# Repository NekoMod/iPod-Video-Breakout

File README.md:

# iPod-Video-Breakout

Breakout board for iPod Video connectors.

It uses our own connectors EAGLE library https://github.com/NekoMod/iPod-Video-Motherboard-Connectors

Pins are raster 2.54mm.

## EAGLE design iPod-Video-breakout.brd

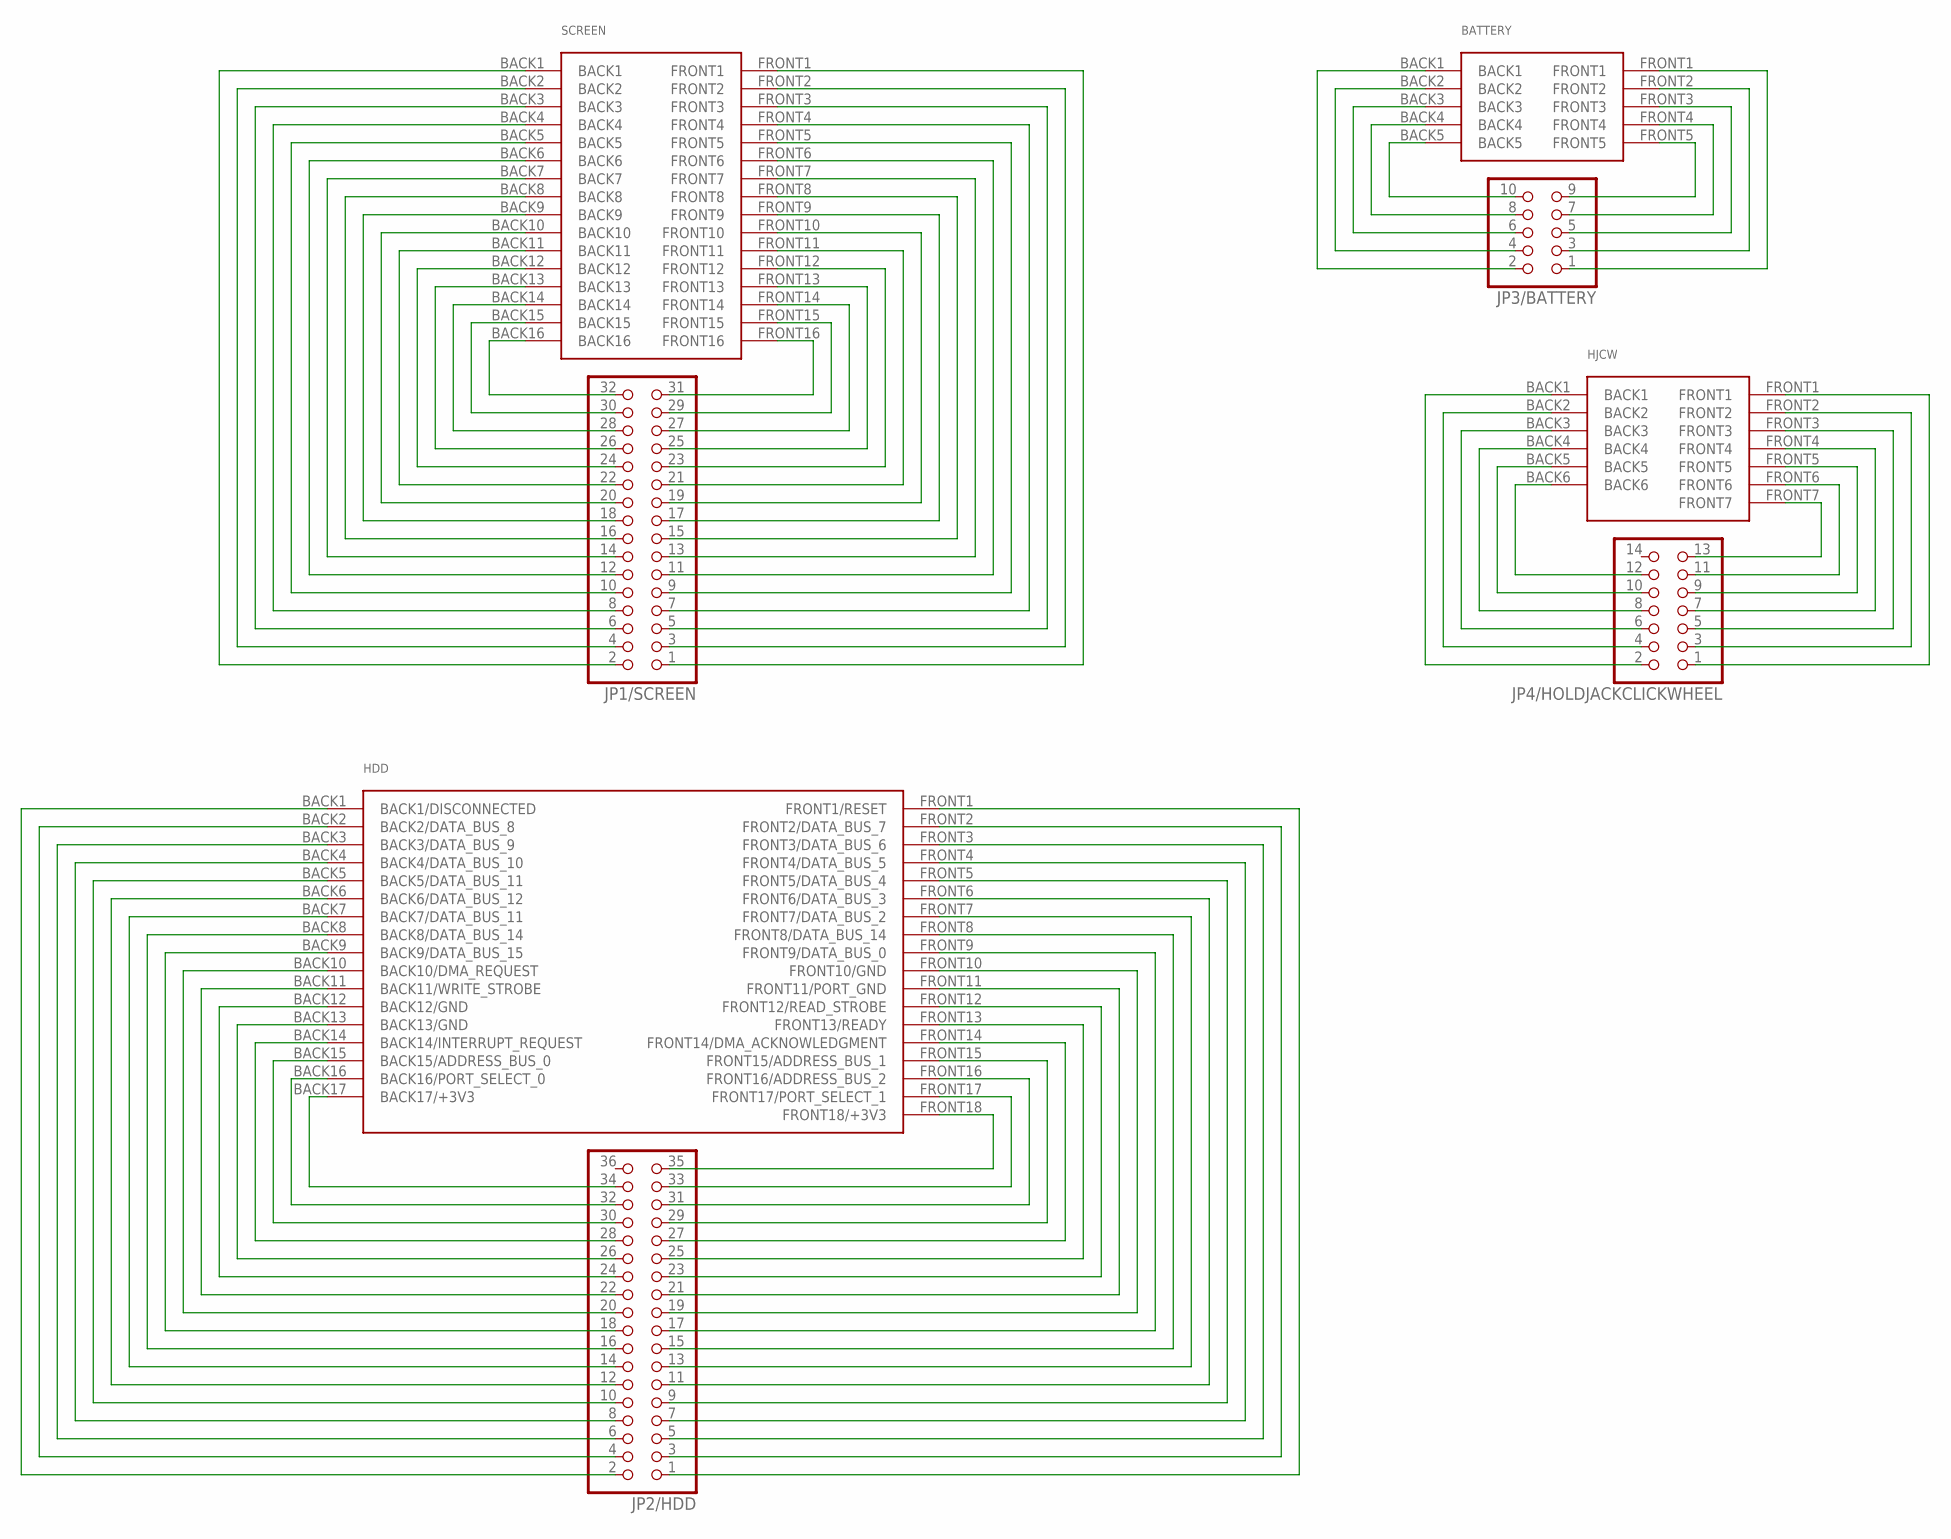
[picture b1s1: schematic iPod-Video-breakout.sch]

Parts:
BATTERY: 526100572/BATTERY; 526100572
HDD: 5035663502/HDD; 5035663502
HJCW: 5035661302/HOLDJACK&CLICKWHEEL; 5035661302
JP1/SCREEN: PINHD-2X16; 2X16
JP2/HDD: PINHD-2X18; 2X18
JP3/BATTERY: PINHD-2X5; 2X05
JP4/HOLDJACKCLICKWHEEL: PINHD-2X7; 2X07
SCREEN: FF12-32A-R11A/SCREEN; FF12-32A-R11A

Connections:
unnamed: JP1/SCREEN.32, SCREEN.BACK16
unnamed: JP1/SCREEN.30, SCREEN.BACK15
unnamed: JP1/SCREEN.28, SCREEN.BACK14
unnamed: JP1/SCREEN.26, SCREEN.BACK13
unnamed: JP1/SCREEN.24, SCREEN.BACK12
unnamed: JP1/SCREEN.22, SCREEN.BACK11
unnamed: JP1/SCREEN.20, SCREEN.BACK10
unnamed: JP1/SCREEN.18, SCREEN.BACK9
unnamed: JP1/SCREEN.16, SCREEN.BACK8
unnamed: JP1/SCREEN.14, SCREEN.BACK7
unnamed: JP1/SCREEN.12, SCREEN.BACK6
unnamed: JP1/SCREEN.10, SCREEN.BACK5
unnamed: JP1/SCREEN.8, SCREEN.BACK4
unnamed: JP1/SCREEN.6, SCREEN.BACK3
unnamed: JP1/SCREEN.4, SCREEN.BACK2
unnamed: JP1/SCREEN.2, SCREEN.BACK1
unnamed: JP1/SCREEN.31, SCREEN.FRONT16
unnamed: JP1/SCREEN.29, SCREEN.FRONT15
unnamed: JP1/SCREEN.27, SCREEN.FRONT14
unnamed: JP1/SCREEN.25, SCREEN.FRONT13
unnamed: JP1/SCREEN.23, SCREEN.FRONT12
unnamed: JP1/SCREEN.21, SCREEN.FRONT11
unnamed: JP1/SCREEN.19, SCREEN.FRONT10
unnamed: JP1/SCREEN.17, SCREEN.FRONT9
unnamed: JP1/SCREEN.15, SCREEN.FRONT8
unnamed: JP1/SCREEN.13, SCREEN.FRONT7
unnamed: JP1/SCREEN.11, SCREEN.FRONT6
unnamed: JP1/SCREEN.9, SCREEN.FRONT5
unnamed: JP1/SCREEN.7, SCREEN.FRONT4
unnamed: JP1/SCREEN.5, SCREEN.FRONT3
unnamed: JP1/SCREEN.3, SCREEN.FRONT2
unnamed: JP1/SCREEN.1, SCREEN.FRONT1
unnamed: HDD.BACK17 (BACK17/+3V3), JP2/HDD.34
unnamed: HDD.BACK16 (BACK16/PORT_SELECT_0), JP2/HDD.32
unnamed: HDD.BACK15 (BACK15/ADDRESS_BUS_0), JP2/HDD.30
unnamed: HDD.BACK14 (BACK14/INTERRUPT_REQUEST), JP2/HDD.28
unnamed: HDD.BACK13 (BACK13/GND), JP2/HDD.26
unnamed: HDD.BACK12 (BACK12/GND), JP2/HDD.24
unnamed: HDD.BACK11 (BACK11/WRITE_STROBE), JP2/HDD.22
unnamed: HDD.BACK10 (BACK10/DMA_REQUEST), JP2/HDD.20
unnamed: HDD.BACK9 (BACK9/DATA_BUS_15), JP2/HDD.18
unnamed: HDD.BACK8 (BACK8/DATA_BUS_14), JP2/HDD.16
unnamed: HDD.BACK7 (BACK7/DATA_BUS_11), JP2/HDD.14
unnamed: HDD.BACK6 (BACK6/DATA_BUS_12), JP2/HDD.12
unnamed: HDD.BACK5 (BACK5/DATA_BUS_11), JP2/HDD.10
unnamed: HDD.BACK4 (BACK4/DATA_BUS_10), JP2/HDD.8
unnamed: HDD.BACK3 (BACK3/DATA_BUS_9), JP2/HDD.6
unnamed: HDD.BACK2 (BACK2/DATA_BUS_8), JP2/HDD.4
unnamed: HDD.BACK1 (BACK1/DISCONNECTED), JP2/HDD.2
unnamed: HDD.FRONT18 (FRONT18/+3V3), JP2/HDD.35
unnamed: HDD.FRONT17 (FRONT17/PORT_SELECT_1), JP2/HDD.33
unnamed: HDD.FRONT16 (FRONT16/ADDRESS_BUS_2), JP2/HDD.31
unnamed: HDD.FRONT15 (FRONT15/ADDRESS_BUS_1), JP2/HDD.29
unnamed: HDD.FRONT14 (FRONT14/DMA_ACKNOWLEDGMENT), JP2/HDD.27
unnamed: HDD.FRONT13 (FRONT13/READY), JP2/HDD.25
unnamed: HDD.FRONT12 (FRONT12/READ_STROBE), JP2/HDD.23
unnamed: HDD.FRONT11 (FRONT11/PORT_GND), JP2/HDD.21
unnamed: HDD.FRONT10 (FRONT10/GND), JP2/HDD.19
unnamed: HDD.FRONT9 (FRONT9/DATA_BUS_0), JP2/HDD.17
unnamed: HDD.FRONT8 (FRONT8/DATA_BUS_14), JP2/HDD.15
unnamed: HDD.FRONT7 (FRONT7/DATA_BUS_2), JP2/HDD.13
unnamed: HDD.FRONT6 (FRONT6/DATA_BUS_3), JP2/HDD.11
unnamed: HDD.FRONT5 (FRONT5/DATA_BUS_4), JP2/HDD.9
unnamed: HDD.FRONT4 (FRONT4/DATA_BUS_5), JP2/HDD.7
unnamed: HDD.FRONT3 (FRONT3/DATA_BUS_6), JP2/HDD.5
unnamed: HDD.FRONT2 (FRONT2/DATA_BUS_7), JP2/HDD.3
unnamed: HDD.FRONT1 (FRONT1/RESET), JP2/HDD.1
unnamed: BATTERY.BACK5, JP3/BATTERY.10
unnamed: BATTERY.BACK4, JP3/BATTERY.8
unnamed: BATTERY.BACK3, JP3/BATTERY.6
unnamed: BATTERY.BACK2, JP3/BATTERY.4
unnamed: BATTERY.BACK1, JP3/BATTERY.2
unnamed: BATTERY.FRONT5, JP3/BATTERY.9
unnamed: BATTERY.FRONT4, JP3/BATTERY.7
unnamed: BATTERY.FRONT3, JP3/BATTERY.5
unnamed: BATTERY.FRONT2, JP3/BATTERY.3
unnamed: BATTERY.FRONT1, JP3/BATTERY.1
unnamed: HJCW.BACK6, JP4/HOLDJACKCLICKWHEEL.12
unnamed: HJCW.BACK5, JP4/HOLDJACKCLICKWHEEL.10
unnamed: HJCW.BACK4, JP4/HOLDJACKCLICKWHEEL.8
unnamed: HJCW.BACK3, JP4/HOLDJACKCLICKWHEEL.6
unnamed: HJCW.BACK2, JP4/HOLDJACKCLICKWHEEL.4
unnamed: HJCW.BACK1, JP4/HOLDJACKCLICKWHEEL.2
unnamed: HJCW.FRONT7, JP4/HOLDJACKCLICKWHEEL.13
unnamed: HJCW.FRONT6, JP4/HOLDJACKCLICKWHEEL.11
unnamed: HJCW.FRONT5, JP4/HOLDJACKCLICKWHEEL.9
unnamed: HJCW.FRONT4, JP4/HOLDJACKCLICKWHEEL.7
unnamed: HJCW.FRONT3, JP4/HOLDJACKCLICKWHEEL.5
unnamed: HJCW.FRONT2, JP4/HOLDJACKCLICKWHEEL.3
unnamed: HJCW.FRONT1, JP4/HOLDJACKCLICKWHEEL.1

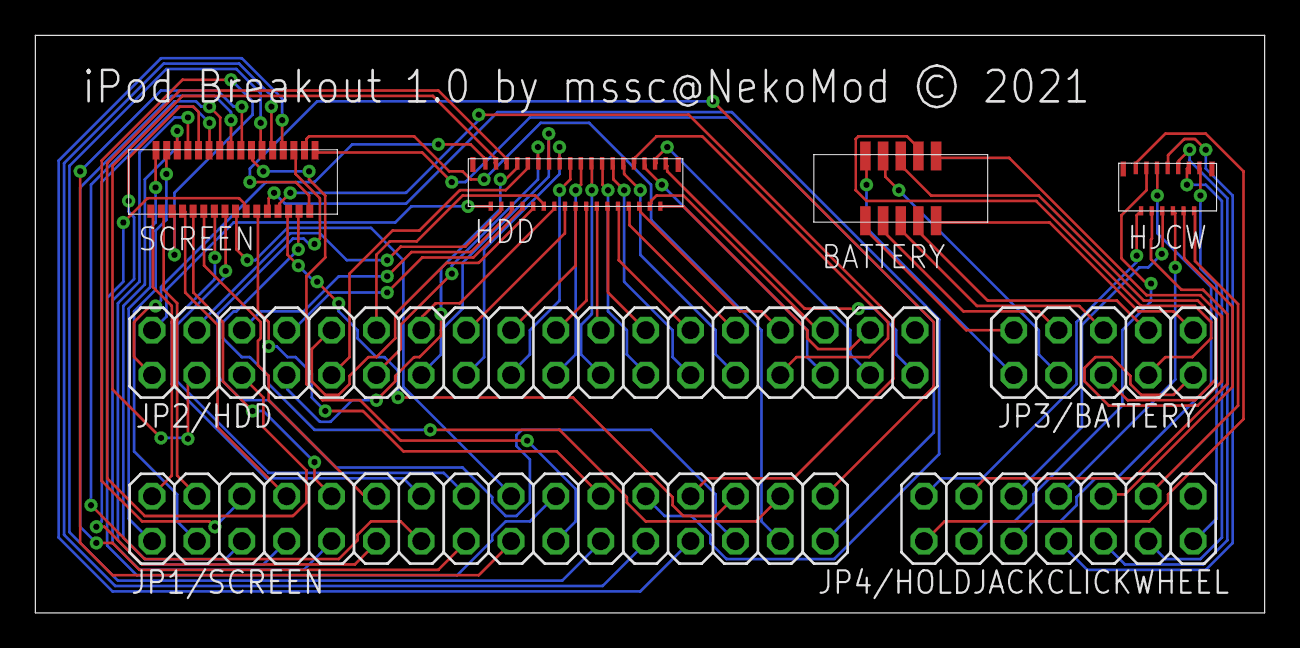
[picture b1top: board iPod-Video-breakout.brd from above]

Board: 2 copper layers, 69.6 x 32.7 mm, 8 parts (0 on the bottom side), 90 nets.

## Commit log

2021-01-28 Newlines
2021-01-28 Added files
2021-01-28 Added render image

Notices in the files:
iPod-Video-breakout.brd:
iPod Breakout 1.0 by mssc@NekoMod © 2021
